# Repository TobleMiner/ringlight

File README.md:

Ring light
==========

Just a quick and dirty, JLCPCB assembly ready ring light with adjustable brightness and color temperature.

Entirely untested. Use at your own risk.

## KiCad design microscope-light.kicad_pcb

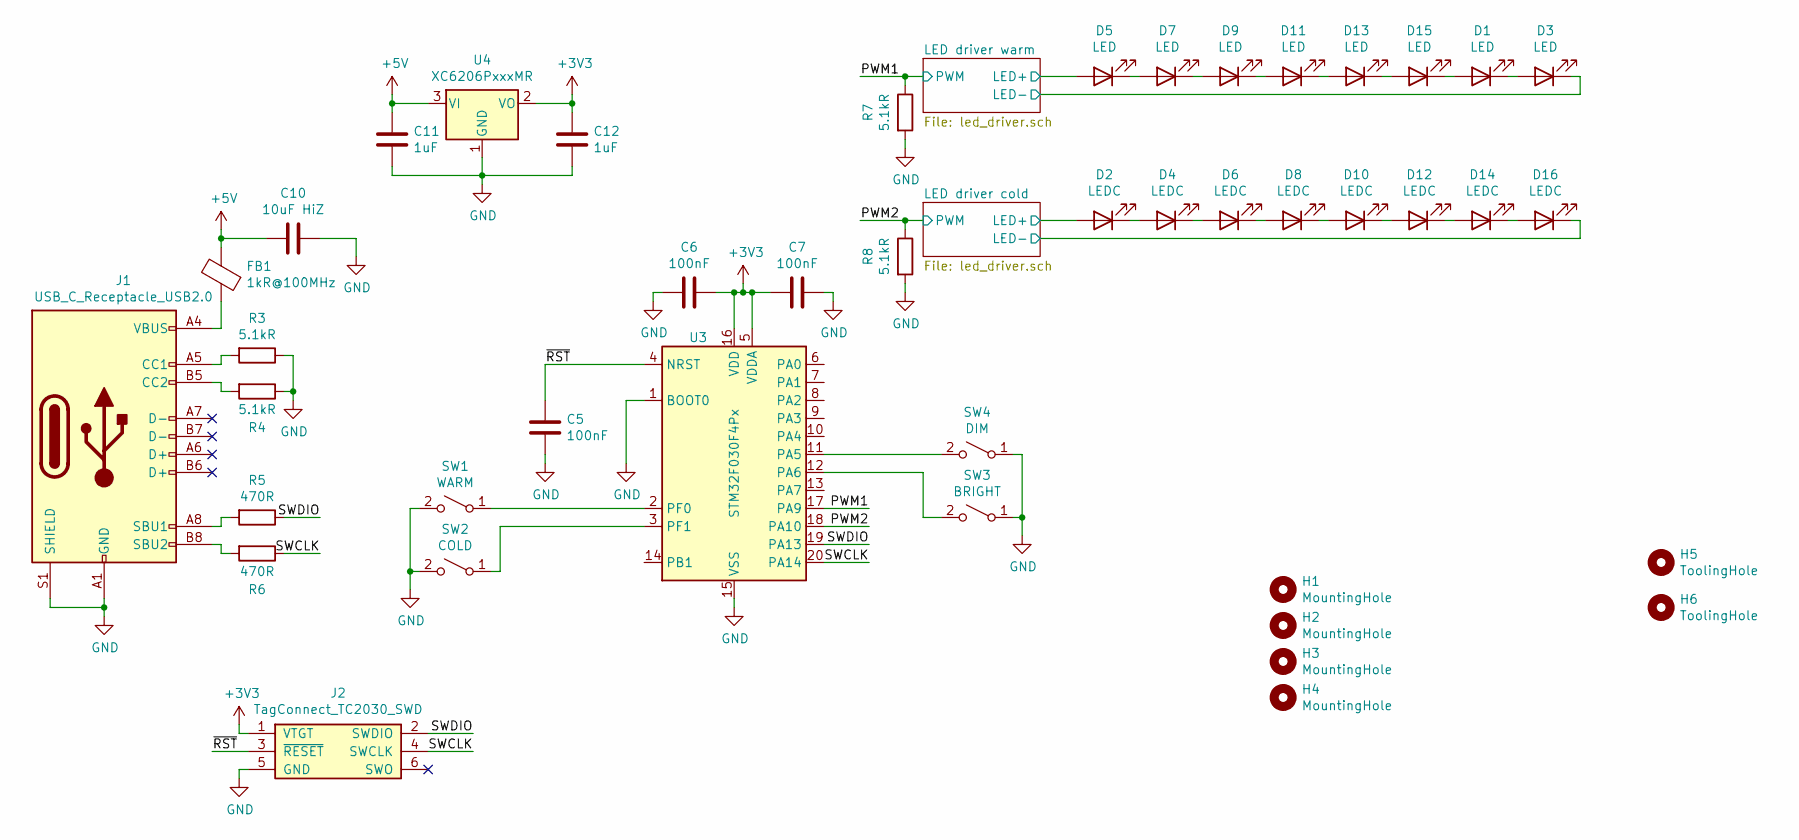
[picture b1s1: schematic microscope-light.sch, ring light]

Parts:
C5, C6, C7: 100nF; C_0402_1005Metric; LCSC C1525
C10: 10uF HiZ; C_1206_3216Metric; LCSC C13585
C11, C12: 1uF; C_0402_1005Metric; LCSC C52923
D1, D3, D5, D7, D9, D11, D13, D15: LED; PLCC-2; LCSC C210310
D2, D4, D6, D8, D10, D12, D14, D16: LEDC; PLCC-2; LCSC C210314
FB1: 1kR@100MHz; L_1206_3216Metric; LCSC C139169
H1, H2, H3, H4: MountingHole; MountingHole_4.3mm_M4
H5, H6: ToolingHole; ToolingHole_JLCSMT
J1: USB_C_Receptacle_USB2.0; USB_C_Receptacle_Palconn_UTC16-G
J2: TagConnect_TC2030_SWD; Tag-Connect_TC2030-IDC-NL_2x03_P1.27mm_Vertical
R3, R4, R7, R8: 5.1kR; R_0402_1005Metric; LCSC C25905
R5, R6: 470R; R_0402_1005Metric; LCSC C25117
SW1: WARM; TS-1187A-X-X-X; LCSC C318889
SW2: COLD; TS-1187A-X-X-X; LCSC C318889
SW3: BRIGHT; TS-1187A-X-X-X; LCSC C318889
SW4: DIM; TS-1187A-X-X-X; LCSC C318889
U3: STM32F030F4Px; TSSOP-20_4.4x6.5mm_P0.65mm; LCSC C89040
U4: XC6206PxxxMR; SOT-23; LCSC C5446

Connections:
+3V3: C6.1, C7.2, C12.1, J2.1 (VTGT), U3.5 (VDDA), U3.16 (VDD), U4.2 (VO)
+5V: C10.2, C11.1, FB1.2, U4.3 (VI); also elsewhere on the board
/LED driver cold/LED+: D2.2 (A); also elsewhere on the board
/LED driver cold/LED-: D16.1 (K); also elsewhere on the board
/LED driver warm/LED+: D5.2 (A); also elsewhere on the board
/LED driver warm/LED-: D3.1 (K); also elsewhere on the board
/PWM1: R7.1, U3.17 (PA9); also elsewhere on the board
/PWM2: R8.1, U3.18 (PA10); also elsewhere on the board
/SWCLK: J2.4 (SWCLK), R6.1, U3.20 (PA14)
/SWDIO: J2.2 (SWDIO), R5.1, U3.19 (PA13)
/~RST: C5.2, J2.3 (~RESET), U3.4 (NRST)
GND: C5.1, C6.2, C7.1, C10.1, C11.2, C12.2, J1.A1 (GND), J1.A12 (GND), J1.B1 (GND), J1.B12 (GND), J1.S1 (SHIELD), J2.5 (GND), R3.1, R4.1, R7.2, R8.2, SW1.2 (B), SW2.2 (B), SW3.1 (A), SW4.1 (A), U3.1 (BOOT0), U3.15 (VSS), U4.1 (GND); also elsewhere on the board
unnamed: D1.1 (K), D3.2 (A)
unnamed: D1.2 (A), D15.1 (K)
unnamed: D2.1 (K), D4.2 (A)
unnamed: D4.1 (K), D6.2 (A)
unnamed: D5.1 (K), D7.2 (A)
unnamed: D6.1 (K), D8.2 (A)
unnamed: D7.1 (K), D9.2 (A)
unnamed: D10.1 (K), D12.2 (A)
unnamed: D8.1 (K), D10.2 (A)
unnamed: D11.1 (K), D13.2 (A)
unnamed: D9.1 (K), D11.2 (A)
unnamed: D12.1 (K), D14.2 (A)
unnamed: D13.1 (K), D15.2 (A)
unnamed: D14.1 (K), D16.2 (A)
unnamed: FB1.1, J1.A4 (VBUS), J1.A9 (VBUS), J1.B4 (VBUS), J1.B9 (VBUS)
unnamed: J1.A5 (CC1), R3.2
unnamed: J1.A8 (SBU1), R5.2
unnamed: J1.B5 (CC2), R4.2
unnamed: J1.B8 (SBU2), R6.2
unnamed: SW1.1 (A), U3.2 (PF0)
unnamed: SW2.1 (A), U3.3 (PF1)
unnamed: SW3.2 (B), U3.12 (PA6)
unnamed: SW4.2 (B), U3.11 (PA5)

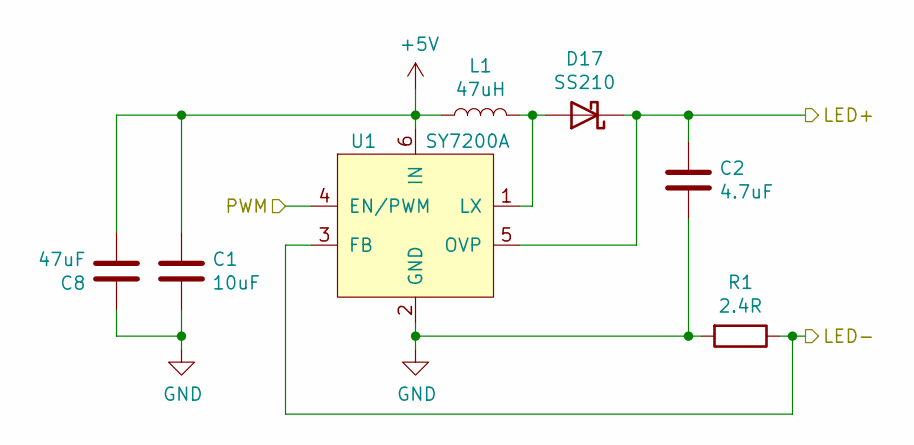
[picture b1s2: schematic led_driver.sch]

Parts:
C1: 10uF; C_0805_2012Metric; LCSC C15850
C2: 4.7uF; C_1206_3216Metric; LCSC C29823
C8: 47uF; C_1206_3216Metric; LCSC C96123
D17: SS210; D_SMA; LCSC C14996
L1: 47uH; MWSA0603S; LCSC C408455
R1: 2.4R; R_0805_2012Metric; LCSC C17528
U1: SY7200A; SOT-23-6; LCSC C107309

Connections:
+5V: C1.1, C8.2, L1.1, U1.6 (IN); also elsewhere on the board
/LED driver warm/LED+: C2.1, D17.1 (K), U1.5 (OVP); also elsewhere on the board
/LED driver warm/LED-: R1.1, U1.3 (FB); also elsewhere on the board
/PWM1: U1.4 (EN/PWM); also elsewhere on the board
GND: C1.2, C2.2, C8.1, R1.2, U1.2 (GND); also elsewhere on the board
unnamed: D17.2 (A), L1.2, U1.1 (LX)

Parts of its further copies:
C3: 10uF; C_0805_2012Metric; LCSC C15850
C4: 4.7uF; C_1206_3216Metric; LCSC C29823
C9: 47uF; C_1206_3216Metric; LCSC C96123
D18: SS210; D_SMA; LCSC C14996
L2: 47uH; MWSA0603S; LCSC C408455
R2: 2.4R; R_0805_2012Metric; LCSC C17528
U2: SY7200A; SOT-23-6; LCSC C107309

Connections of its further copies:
+5V: C3.1, C9.2, L2.1, U2.6 (IN); also elsewhere on the board
/LED driver cold/LED+: C4.1, D18.1 (K), U2.5 (OVP); also elsewhere on the board
/LED driver cold/LED-: R2.1, U2.3 (FB); also elsewhere on the board
/PWM2: U2.4 (EN/PWM); also elsewhere on the board
GND: C3.2, C4.2, C9.1, R2.2, U2.2 (GND); also elsewhere on the board
unnamed: D18.2 (A), L2.2, U2.1 (LX)

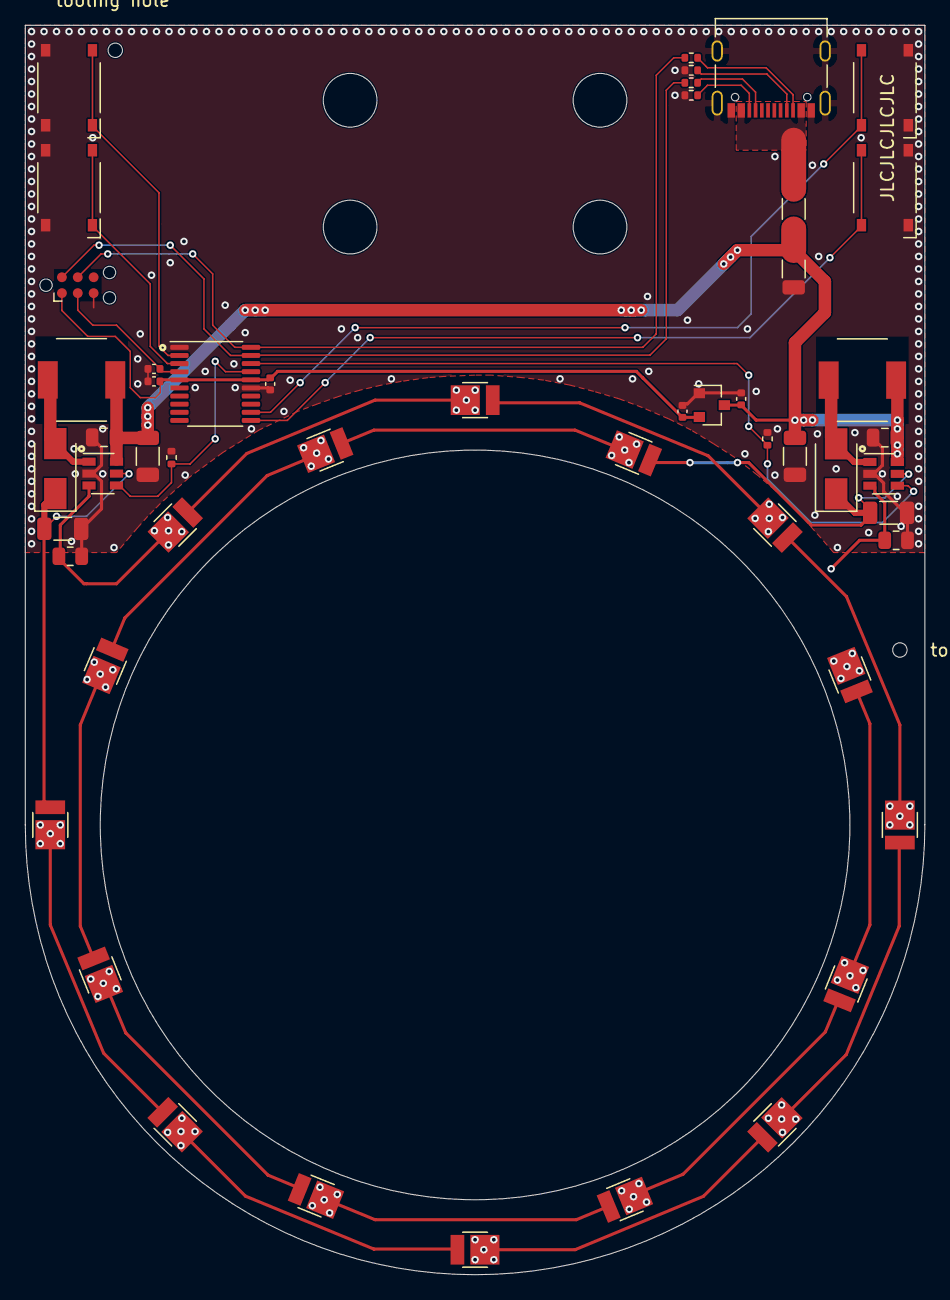
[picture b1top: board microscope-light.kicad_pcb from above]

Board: 2 copper layers, 72.0 x 100.0 mm, 57 parts (0 on the bottom side), 37 nets.

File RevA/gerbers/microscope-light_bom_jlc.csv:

"Comment","Designator","Footprint","LCSC Part #"
"10uF","C1,C3","C_0805_2012Metric","C15850"
"4.7uF","C2,C4","C_1206_3216Metric","C29823"
"100nF","C7,C6,C5","C_0402_1005Metric","C1525"
"47uF","C8,C9","C_1206_3216Metric","C96123"
"10uF HiZ","C10","C_1206_3216Metric","C13585"
"1uF","C11,C12","C_0402_1005Metric","C52923"
"LED","D1,D3,D5,D7,D9,D11,D13,D15","PLCC-2","C210310"
"LEDC","D2,D4,D6,D8,D10,D12,D14,D16","PLCC-2","C210314"
"SS210","D17,D18","D_SMA","C14996"
"1kR@100MHz","FB1","L_1206_3216Metric","C139169"
"47uH","L1,L2","MWSA0603S","C408455"
"2.4R","R1,R2","R_0805_2012Metric","C17528"
"5.1kR","R3,R4,R7,R8","R_0402_1005Metric","C25905"
"470R","R5,R6","R_0402_1005Metric","C25117"
"WARM","SW1","TS-1187A-X-X-X","C318889"
"COLD","SW2","TS-1187A-X-X-X","C318889"
"BRIGHT","SW3","TS-1187A-X-X-X","C318889"
"DIM","SW4","TS-1187A-X-X-X","C318889"
"SY7200A","U1,U2","SOT-23-6","C107309"
"STM32F030F4Px","U3","TSSOP-20_4.4x6.5mm_P0.65mm","C89040"
"XC6206PxxxMR","U4","SOT-23","C5446"

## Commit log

2020-12-30 Hide fp references
2020-12-30 Add fabrication features
2020-12-30 Add schematic export
2020-12-30 Add fabrication files
2020-12-30 Add README
2020-12-30 Add license
2021-01-15 Add firmware submodule
